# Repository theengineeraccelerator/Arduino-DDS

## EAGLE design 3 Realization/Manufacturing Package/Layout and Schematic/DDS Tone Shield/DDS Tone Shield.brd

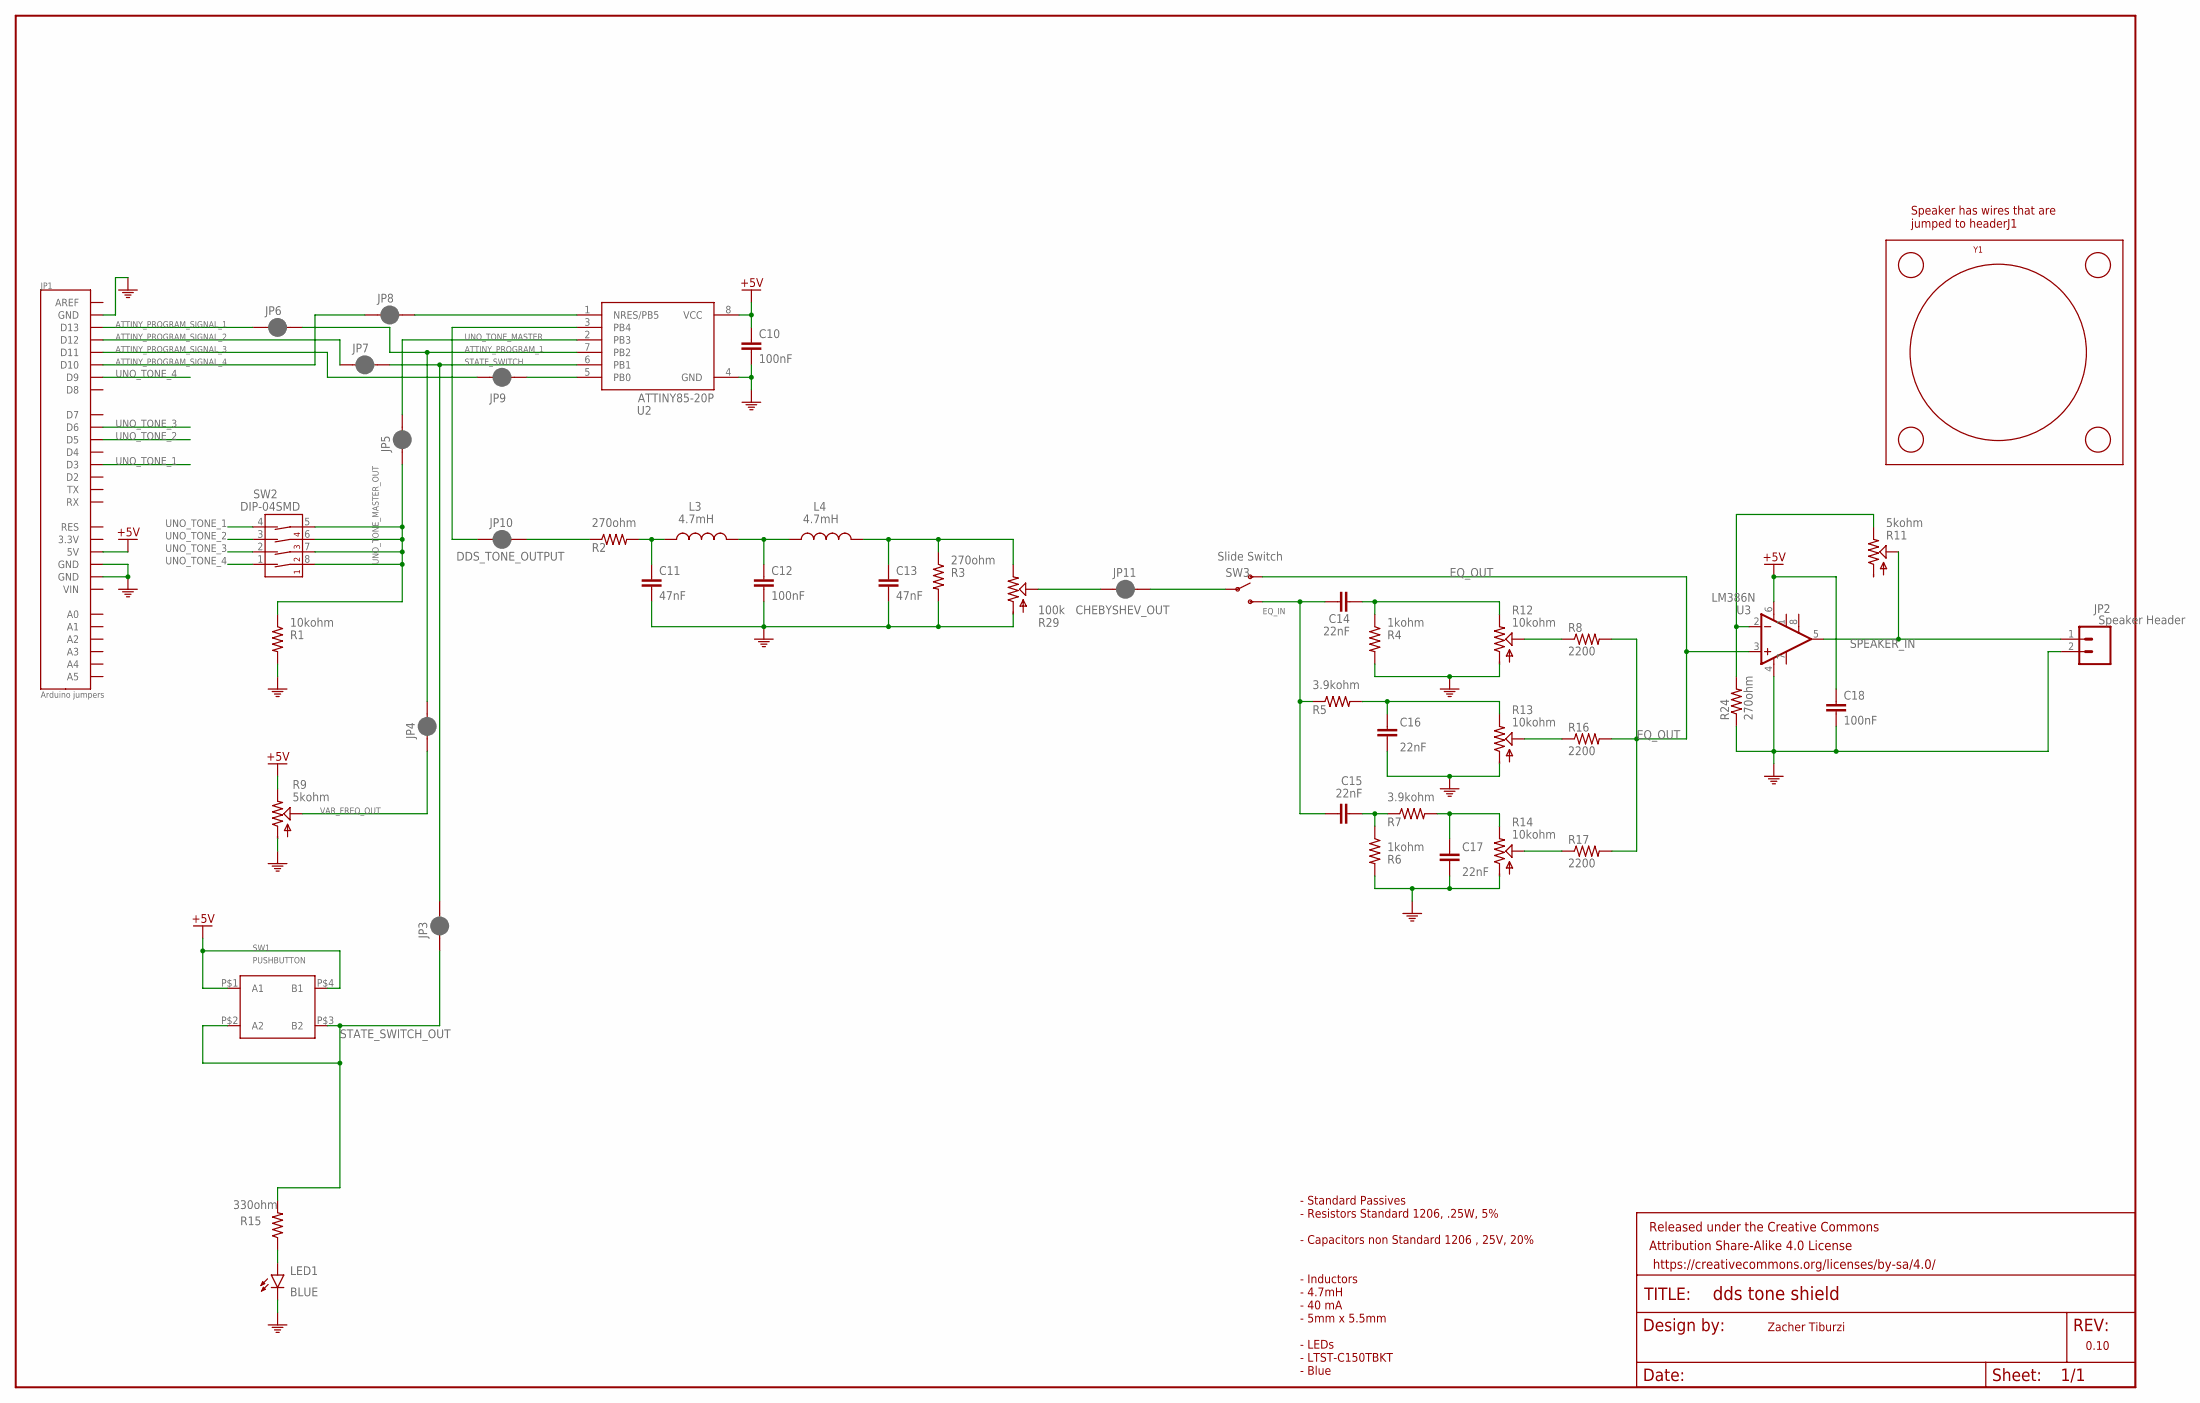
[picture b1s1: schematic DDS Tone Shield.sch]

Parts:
C10, C12, C18: 100nF; EIA3216
C11, C13: 47nF; EIA3216
C14, C15, C16, C17: 22nF; EIA3216
FRAME2: FRAME-LEDGER; CREATIVE_COMMONS
JP1: Arduino jumpers; DUEMILANOVE_SHIELD
JP2: Speaker Header; 1X02
JP3, JP4, JP5, JP6, JP7, JP8, JP9, JP10, JP11: JUMPER-SMT_2_NC_PASTE_SILK; SMT-JUMPER_2_NC_PASTE_SILK
L3, L4: 4.7mH; SDR0503-472JL
LED1: BLUE; LED-1206
R1: 10kohm; 1206
R2, R3, R24: 270ohm; 1206
R4, R6: 1kohm; 1206
R5, R7: 3.9kohm; 1206
R8, R16, R17: 2200; 1206
R9, R11: 5kohm; RK09K/RK09D_SERIES
R12, R13, R14: 10kohm; RK09K/RK09D_SERIES
R15: 330ohm; 1206
R29: 100k; RK09K/RK09D_SERIES
SW1: PUSHBUTTON; 3CSH9_MEC_PUSHBUTTON
SW2: DIP-04SMD; DIPSWITCH-04-SMD
SW3: Slide Switch; JS102011SAQN
U2: ATTINY85-20P; PDIP08_300MIL
U3: LM386N; DIP08
Y1: Speaker; CSS-40408N

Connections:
+5V: C10.A (1), C18.A (1), JP1.5V, R9.P$3 (E), SW1.P$1 (A1), SW1.P$4 (B1), U2.8 (VCC), U3.6 (V+)
AMP_NEG: R11.P$3 (E), R24.2, U3.2 (-IN)
ATTINY_PROGRAM_1: JP4.2, JP6.2, U2.7 (PB2)
ATTINY_PROGRAM_SIGNAL_1: JP1.D13, JP6.1
ATTINY_PROGRAM_SIGNAL_2: JP1.D12, JP7.1
ATTINY_PROGRAM_SIGNAL_3: JP1.D11, JP9.1
ATTINY_PROGRAM_SIGNAL_4: JP1.D10, JP8.1
BPF_ATTENUATED: R14.P$2 (S), R17.1
BPF_INTERMEDIATE: C15.C (2), R6.1, R7.1
BPF_OUT: C17.A (1), R7.2, R14.P$3 (E)
CHEBYSHEV_IN: JP10.2, R2.1
CHEBYSHEV_OUT: JP11.1, R29.P$2 (S)
CHEBYSHEV_STAGE_1: C11.A (1), L3.P$1 (1), R2.2
CHEBYSHEV_STAGE_2: C12.A (1), L3.P$2 (2), L4.P$1 (1)
CHEBYSHEV_STAGE_3: C13.A (1), L4.P$2 (2), R3.1, R29.P$3 (E)
DDS_TONE_OUTPUT: JP10.1, U2.3 (PB4)
EQ_IN: C14.A (1), C15.A (1), R5.1, SW3.P$1 (S)
EQ_OUT: R8.2, R16.2, R17.2, SW3.P$2 (O), U3.3 (+IN)
GND: C10.C (2), C11.C (2), C12.C (2), C13.C (2), C16.C (2), C17.C (2), C18.C (2), JP1.GND@0 (GND), JP1.GND@1 (GND), JP1.GND@2 (GND), JP2.2, LED1.C, R1.2, R3.2, R4.2, R6.2, R9.P$1 (A), R12.P$1 (A), R13.P$1 (A), R14.P$1 (A), R24.1, R29.P$1 (A), U2.4 (GND), U3.4 (V-)
HPF_ATTENUATED: R8.1, R12.P$2 (S)
HPF_OUT: C14.C (2), R4.1, R12.P$3 (E)
LED_POSITIVE: LED1.A, R15.1
LPF_ATTENUATED: R13.P$2 (S), R16.1
LPF_OUT: C16.A (1), R5.2, R13.P$3 (E)
PROGRAM3: JP9.2, U2.5 (PB0)
PROGRAM4: JP8.2, U2.1 (NRES/PB5)
SLIDE_SWITCH_IN: JP11.2, SW3.P$3
SPEAKER_IN: JP2.1, R11.P$2 (S), U3.5 (OUT)
STATE_SWITCH: JP3.2, JP7.2, U2.6 (PB1)
STATE_SWITCH_OUT: JP3.1, R15.2, SW1.P$2 (A2), SW1.P$3 (B2)
UNO_TONE_1: JP1.D3, SW2.4 (4A)
UNO_TONE_2: JP1.D5, SW2.3 (3A)
UNO_TONE_3: JP1.D6, SW2.2 (2A)
UNO_TONE_4: JP1.D9, SW2.1 (1A)
UNO_TONE_MASTER: JP5.2, U2.2 (PB3)
UNO_TONE_MASTER_OUT: JP5.1, R1.1, SW2.5 (4B), SW2.6 (3B), SW2.7 (2B), SW2.8 (1B)
VAR_FREQ_OUT: JP4.1, R9.P$2 (S)

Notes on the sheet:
Zacher Tiburzi
Speaker has wires that are jumped to headerJ1
- Standard Passives - Resistors Standard 1206, .25W, 5% - Capacitors non Standard 1206 , 25V, 20% - Inductors - 4.7mH - 40 mA - 5mm x 5.5mm - LEDs - LTST-C150TBKT - Blue

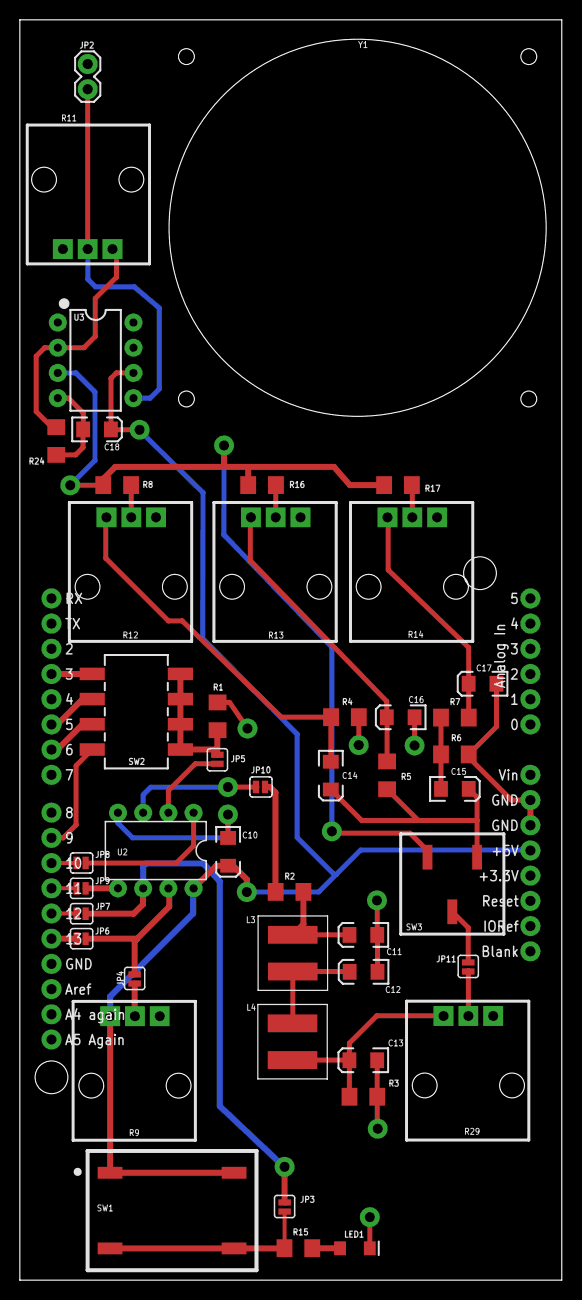
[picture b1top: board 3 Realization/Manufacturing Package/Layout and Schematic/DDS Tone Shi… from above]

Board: 2 copper layers, 54.6 x 127.0 mm, 48 parts (0 on the bottom side), 37 nets.

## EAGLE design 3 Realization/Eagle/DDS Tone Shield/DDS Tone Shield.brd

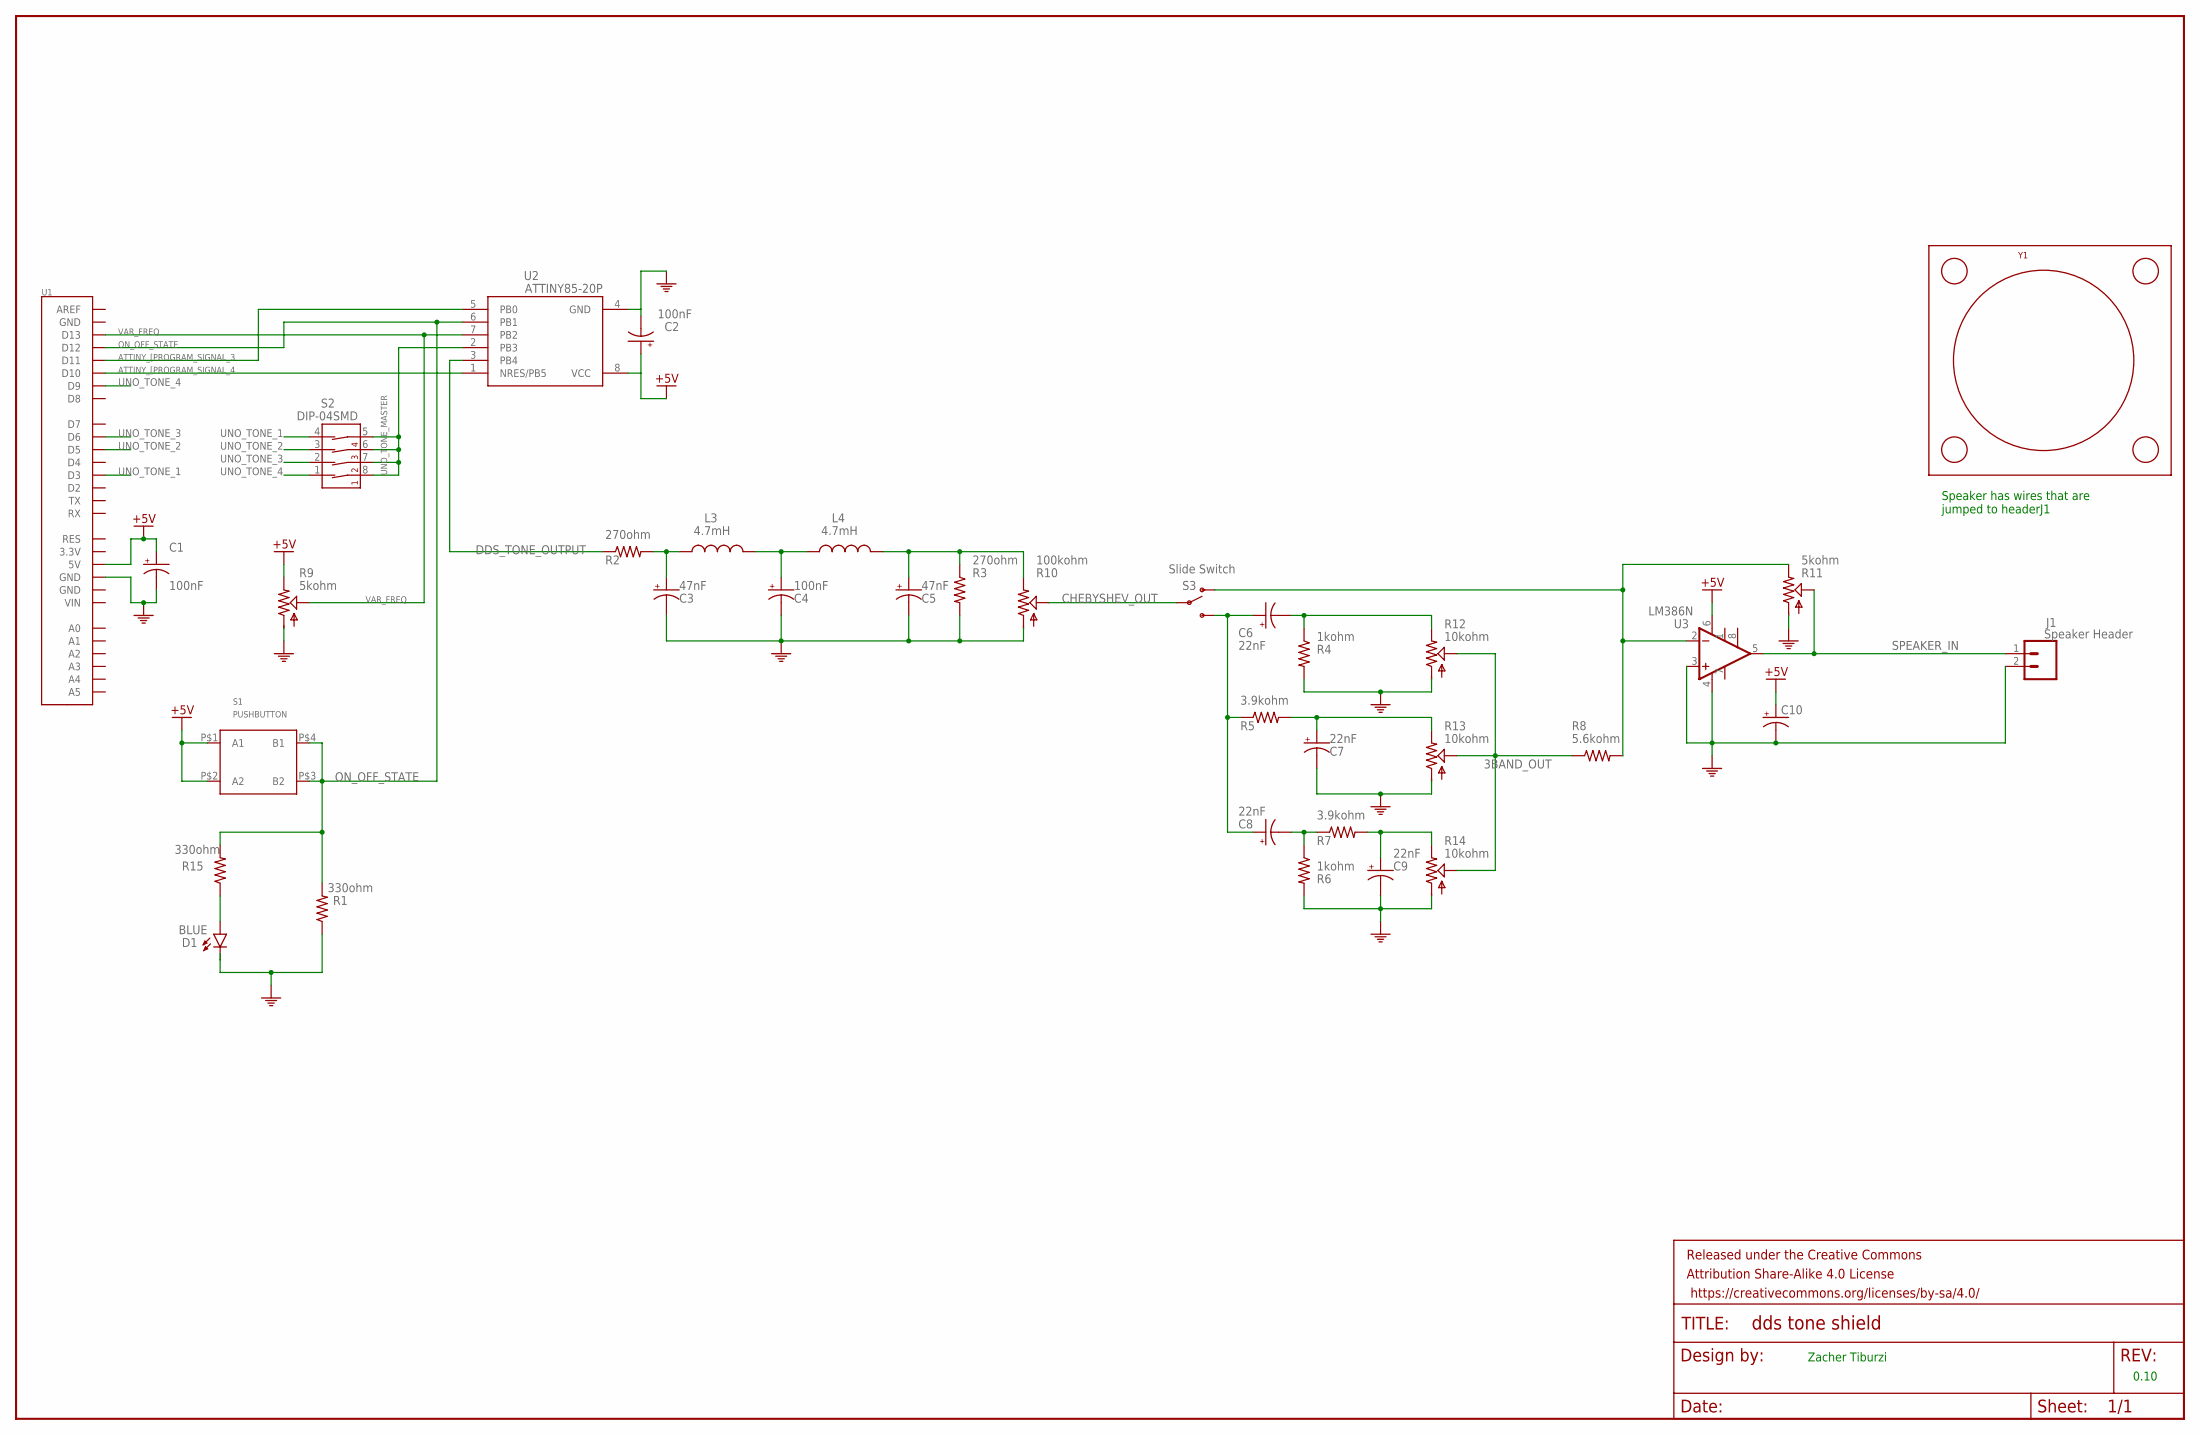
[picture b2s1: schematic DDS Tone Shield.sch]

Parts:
C1, C2, C4: 100nF; EIA3216
C3, C5: 47nF; EIA3216
C6, C7, C8, C9: 22nF; EIA3216
C10: CAP_POL1206; EIA3216
D1: BLUE; LED-1206
FRAME2: FRAME-LEDGER; CREATIVE_COMMONS
J1: Speaker Header; 1X02
L3, L4: 4.7mH; SDR0503-472JL
R1, R15: 330ohm; 1206
R2, R3: 270ohm; 1206
R4, R6: 1kohm; 1206
R5, R7: 3.9kohm; 1206
R8: 5.6kohm; 1206
R9, R11: 5kohm; RK09K/RK09D_SERIES
R10: 100kohm; 5150500311
R12, R13, R14: 10kohm; RK09K/RK09D_SERIES
S1: PUSHBUTTON; 3CSH9_MEC_PUSHBUTTON
S2: DIP-04SMD; DIPSWITCH-04-SMD
S3: Slide Switch; JS102011SAQN
U1: ARDUINO_SHIELD; DUEMILANOVE_SHIELD
U2: ATTINY85-20P; PDIP08_300MIL
U3: LM386N; DIP08
Y1: SPEAKER; CSS-40408N

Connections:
3BAND_OUT: R8.1, R12.P$2 (S), R13.P$2 (S), R14.P$2 (S)
+5V: C1.A (+), C2.A (+), C10.A (+), R9.P$3 (E), S1.P$1 (A1), S1.P$2 (A2), U1.5V, U2.8 (VCC), U3.6 (V+)
ATTINY_[PROGRAM_SIGNAL_3: U1.D11, U2.5 (PB0)
ATTINY_[PROGRAM_SIGNAL_4: U1.D10, U2.1 (NRES/PB5)
CHEBYSHEV_OUT: R10.P$20 (S), S3.P$3
DDS_TONE_OUTPUT: R2.1, U2.3 (PB4)
GND: C1.C (-), C2.C (-), C3.C (-), C4.C (-), C5.C (-), C7.C (-), C9.C (-), C10.C (-), D1.C, J1.2, R1.1, R3.2, R4.2, R6.2, R9.P$1 (A), R10.P$10 (A), R11.P$1 (A), R12.P$1 (A), R13.P$1 (A), R14.P$1 (A), U1.GND@1 (GND), U2.4 (GND), U3.3 (+IN), U3.4 (V-)
unnamed: D1.A, R15.1
unnamed: C3.A (+), L3.P$1 (1), R2.2
unnamed: C4.A (+), L3.P$2 (2), L4.P$1 (1)
unnamed: C5.A (+), L4.P$2 (2), R3.1, R10.P$30 (E)
unnamed: R8.2, R11.P$3 (E), S3.P$2 (O), U3.2 (-IN)
unnamed: C6.C (-), R4.1, R12.P$3 (E)
unnamed: C7.A (+), R5.2, R13.P$3 (E)
unnamed: C8.C (-), R6.1, R7.1
unnamed: C9.A (+), R7.2, R14.P$3 (E)
unnamed: C6.A (+), C8.A (+), R5.1, S3.P$1 (S)
ON_OFF_STATE: R1.2, R15.2, S1.P$3 (B2), S1.P$4 (B1), U1.D12, U2.6 (PB1)
SPEAKER_IN: J1.1, R11.P$2 (S), U3.5 (OUT)
UNO_TONE_1: S2.4 (4A), U1.D3
UNO_TONE_2: S2.3 (3A), U1.D5
UNO_TONE_3: S2.2 (2A), U1.D6
UNO_TONE_4: S2.1 (1A), U1.D9
UNO_TONE_MASTER: S2.5 (4B), S2.6 (3B), S2.7 (2B), S2.8 (1B), U2.2 (PB3)
VAR_FREQ: R9.P$2 (S), U1.D13, U2.7 (PB2)

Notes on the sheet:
Zacher Tiburzi
Speaker has wires that are jumped to headerJ1

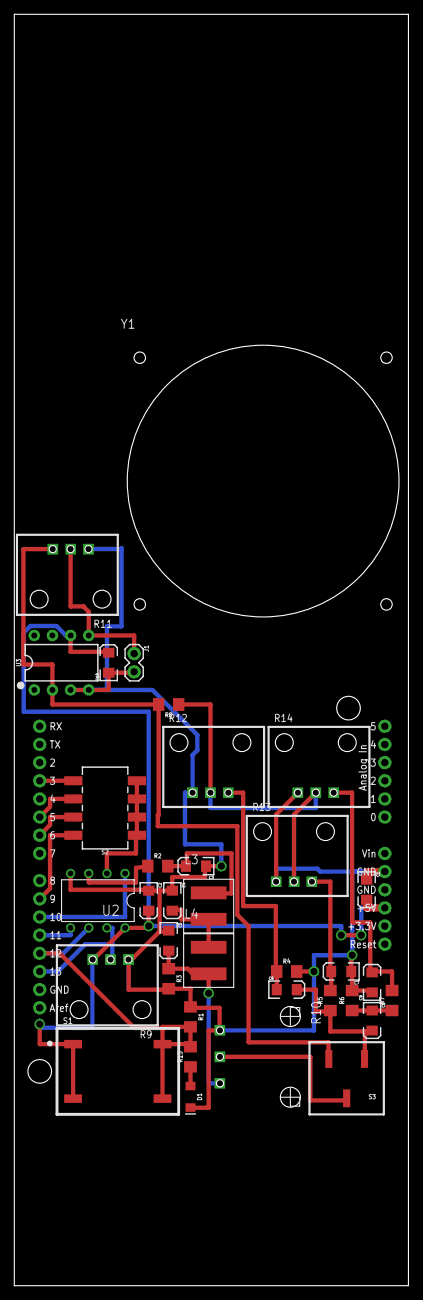
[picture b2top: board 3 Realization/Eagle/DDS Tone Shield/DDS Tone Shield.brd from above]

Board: 2 copper layers, 55.1 x 177.8 mm, 37 parts (0 on the bottom side), 25 nets.

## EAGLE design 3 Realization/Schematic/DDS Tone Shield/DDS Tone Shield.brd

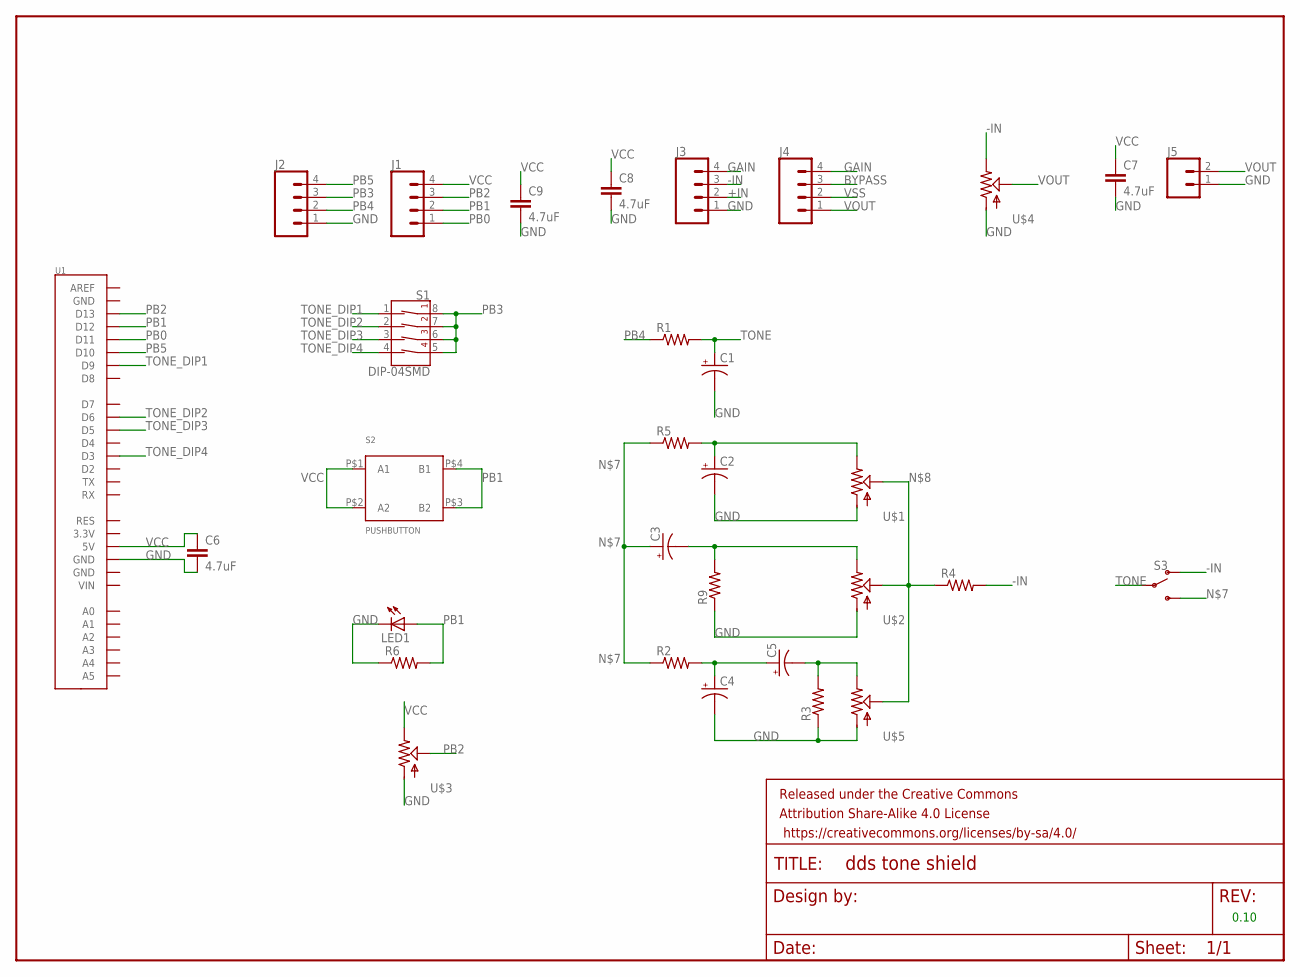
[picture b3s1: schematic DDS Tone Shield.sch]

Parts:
C1, C2, C3, C4, C5: CAP_POL1206; EIA3216
C6, C7, C8, C9: 4.7uF; 1206
FRAME1: FRAME-LETTERNO_PACKAGE; DUMMY
J1, J2, J3, J4: CONN_04; 1X04
J5: CONN_02; 1X02
LED1: LED1206; LED-1206
R1, R2, R3, R4, R5, R6, R9: RESISTOR1206; 1206
S1: DIP-04SMD; DIPSWITCH-04-SMD
S2: PUSHBUTTON; 3CSH9_MEC_PUSHBUTTON
S3: SWITCH-SPDT; JS102011SAQN
U1: ARDUINO_SHIELD; DUEMILANOVE_SHIELD
U$1, U$2, U$3, U$4, U$5: POT1; RK09K/RK09D_SERIES

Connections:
+IN: J3.2
-IN: J3.3, R4.2, S3.P$2 (O), U$4.P$3 (E)
BYPASS: J4.3
GAIN: J3.4, J4.4
GND: C1.C (-), C2.C (-), C4.C (-), C6.2, C7.2, C8.2, C9.2, J2.1, J3.1, J5.1, LED1.C, R3.1, R6.1, R9.1, U1.GND@1 (GND), U$1.P$1 (A), U$2.P$1 (A), U$3.P$1 (A), U$4.P$1 (A), U$5.P$1 (A)
unnamed: C2.A (+), R5.2, U$1.P$3 (E)
unnamed: C4.A (+), C5.A (+), R2.2
unnamed: C3.C (-), R9.2, U$2.P$3 (E)
unnamed: C5.C (-), R3.2, U$5.P$3 (E)
unnamed: C3.A (+), R2.1, R5.1, S3.P$1 (S)
unnamed: R4.1, U$1.P$2 (S), U$5.P$2 (S)
PB0: J1.1, U1.D11
PB1: J1.2, LED1.A, R6.2, S2.P$3 (B2), S2.P$4 (B1), U1.D12
PB2: J1.3, U1.D13, U$3.P$2 (S)
PB3: J2.3, S1.5 (4B), S1.6 (3B), S1.7 (2B), S1.8 (1B)
PB4: J2.2, R1.1
PB5: J2.4, U1.D10
TONE: C1.A (+), R1.2, S3.P$3
TONE_DIP1: S1.1 (1A), U1.D9
TONE_DIP2: S1.2 (2A), U1.D6
TONE_DIP3: S1.3 (3A), U1.D5
TONE_DIP4: S1.4 (4A), U1.D3
VCC: C6.1, C7.1, C8.1, C9.1, J1.4, S2.P$1 (A1), S2.P$2 (A2), U1.5V, U$3.P$3 (E)
VOUT: J4.1, J5.2, U$4.P$2 (S)
VSS: J4.2

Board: 2 copper layers, 32 parts (0 on the bottom side), 22 nets, no tracks yet.

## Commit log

2016-10-17 Moving project to general project folder
2016-10-18 Time estimate
    Initial time estimate for future work without Testing filled in
2016-10-20 Updated Repository; Overhauled timesheet estimate
2016-10-20 Updated Folder Structure
2016-10-20 Different version of PCDDOC laptop
2016-10-20 Bring up for board 2 complete
2016-11-11 Updated realization folder wtih higher Shield Revs and other MSC files
2016-11-11 Added Test Writeup, Code for attiny
    Added base firmware for attiny85 under architecture.
    Added a single point test writeup for signal seen.
    Added screenshots of signals to show what was generated.
    Commented code
2016-11-11 Updated Test writeup
    Added note to show where relevant files are located for the test writeup
2017-05-16 Product Definition Version 03
    Updates to the Product Definition - Zacher Tiburzi 5-16-17
2017-05-19 Product Def. Feedback Resolved
    Updates to the Product Def. that resolve issues written in feedback
    document.
2017-05-19 Spell Check
    Fixed spelling errors.
2017-05-22 restore last changes from Douglas
2017-05-23 Architecture
    Major update to the Architecture files.
2017-05-30 Architecture Update
    Architecture Update
2017-06-27 archatecture / realization
    Clean up the archatecture and work done to the relization
2017-07-08 layout changes
    Layout changes and BOM additions
2017-07-08 Layout changes again
    Layout changes again
2017-07-16 Layout changes
    Layout changes
2017-08-05 layout
    layout
2017-08-25 Revert "restore last changes from Douglas"
    This reverts commit fe8e9e2b7e6a1e2b61edefbca5f57cdcf2c6712e.
2017-09-01 doneeeeeeeeeeeeeeeeeeeeeeee???????????:) :(

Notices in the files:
parts and their libraries:
1-Generic: Released under the Creative Commons Attribution Share-Alike 4.0 License
1-Generic: https://creativecommons.org/licenses/by-sa/4.0
1-Generic: Released under the Creative Commons
